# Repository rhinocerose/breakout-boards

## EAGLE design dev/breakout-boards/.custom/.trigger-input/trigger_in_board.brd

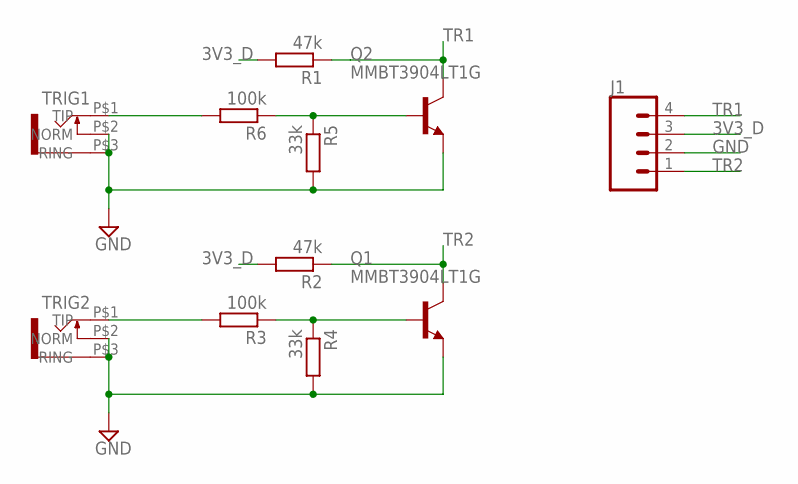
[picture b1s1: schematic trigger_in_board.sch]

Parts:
J1: CONN_04LOCK; 1X04_LOCK
Q1, Q2: MMBT3904LT1G; TRANSISTOR_SOT23-BEC
R1, R2: 47k; R0603
R3, R6: 100k; R0603
R4, R5: 33k; R0603
TRIG1, TRIG2: JACK_KOBICONN_PJM301DM_V2; KOBICONN_PJM301DM_JACK

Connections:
3V3_D: J1.3, R1.2, R2.2
GND: J1.2, Q1.E, Q2.E, R4.2, R5.2, TRIG1.P$2 (NORM), TRIG1.P$3 (RING), TRIG2.P$2 (NORM), TRIG2.P$3 (RING)
unnamed: R6.2, TRIG1.P$1 (TIP)
unnamed: Q2.B, R5.1, R6.1
unnamed: R3.2, TRIG2.P$1 (TIP)
unnamed: Q1.B, R3.1, R4.1
TR1: J1.4, Q2.C, R1.1
TR2: J1.1, Q1.C, R2.1

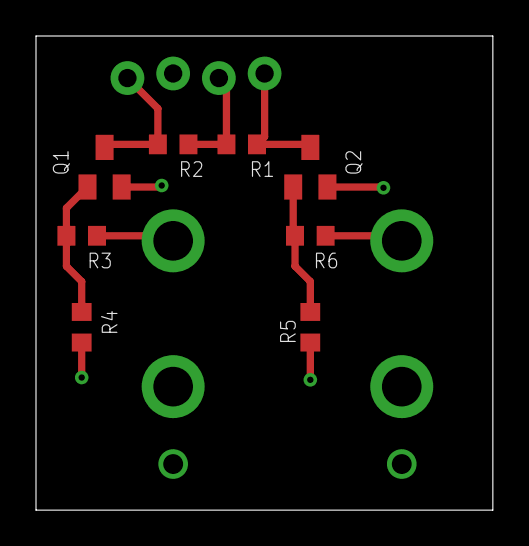
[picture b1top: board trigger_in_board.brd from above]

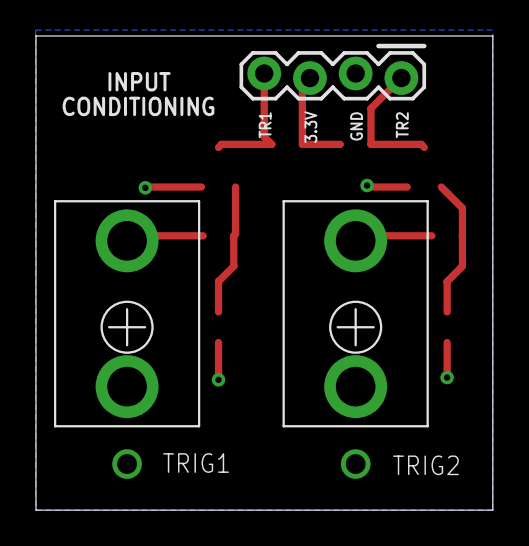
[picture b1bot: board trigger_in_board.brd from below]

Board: 2 copper layers, 25.4 x 26.3 mm, 11 parts (3 on the bottom side), 8 nets.

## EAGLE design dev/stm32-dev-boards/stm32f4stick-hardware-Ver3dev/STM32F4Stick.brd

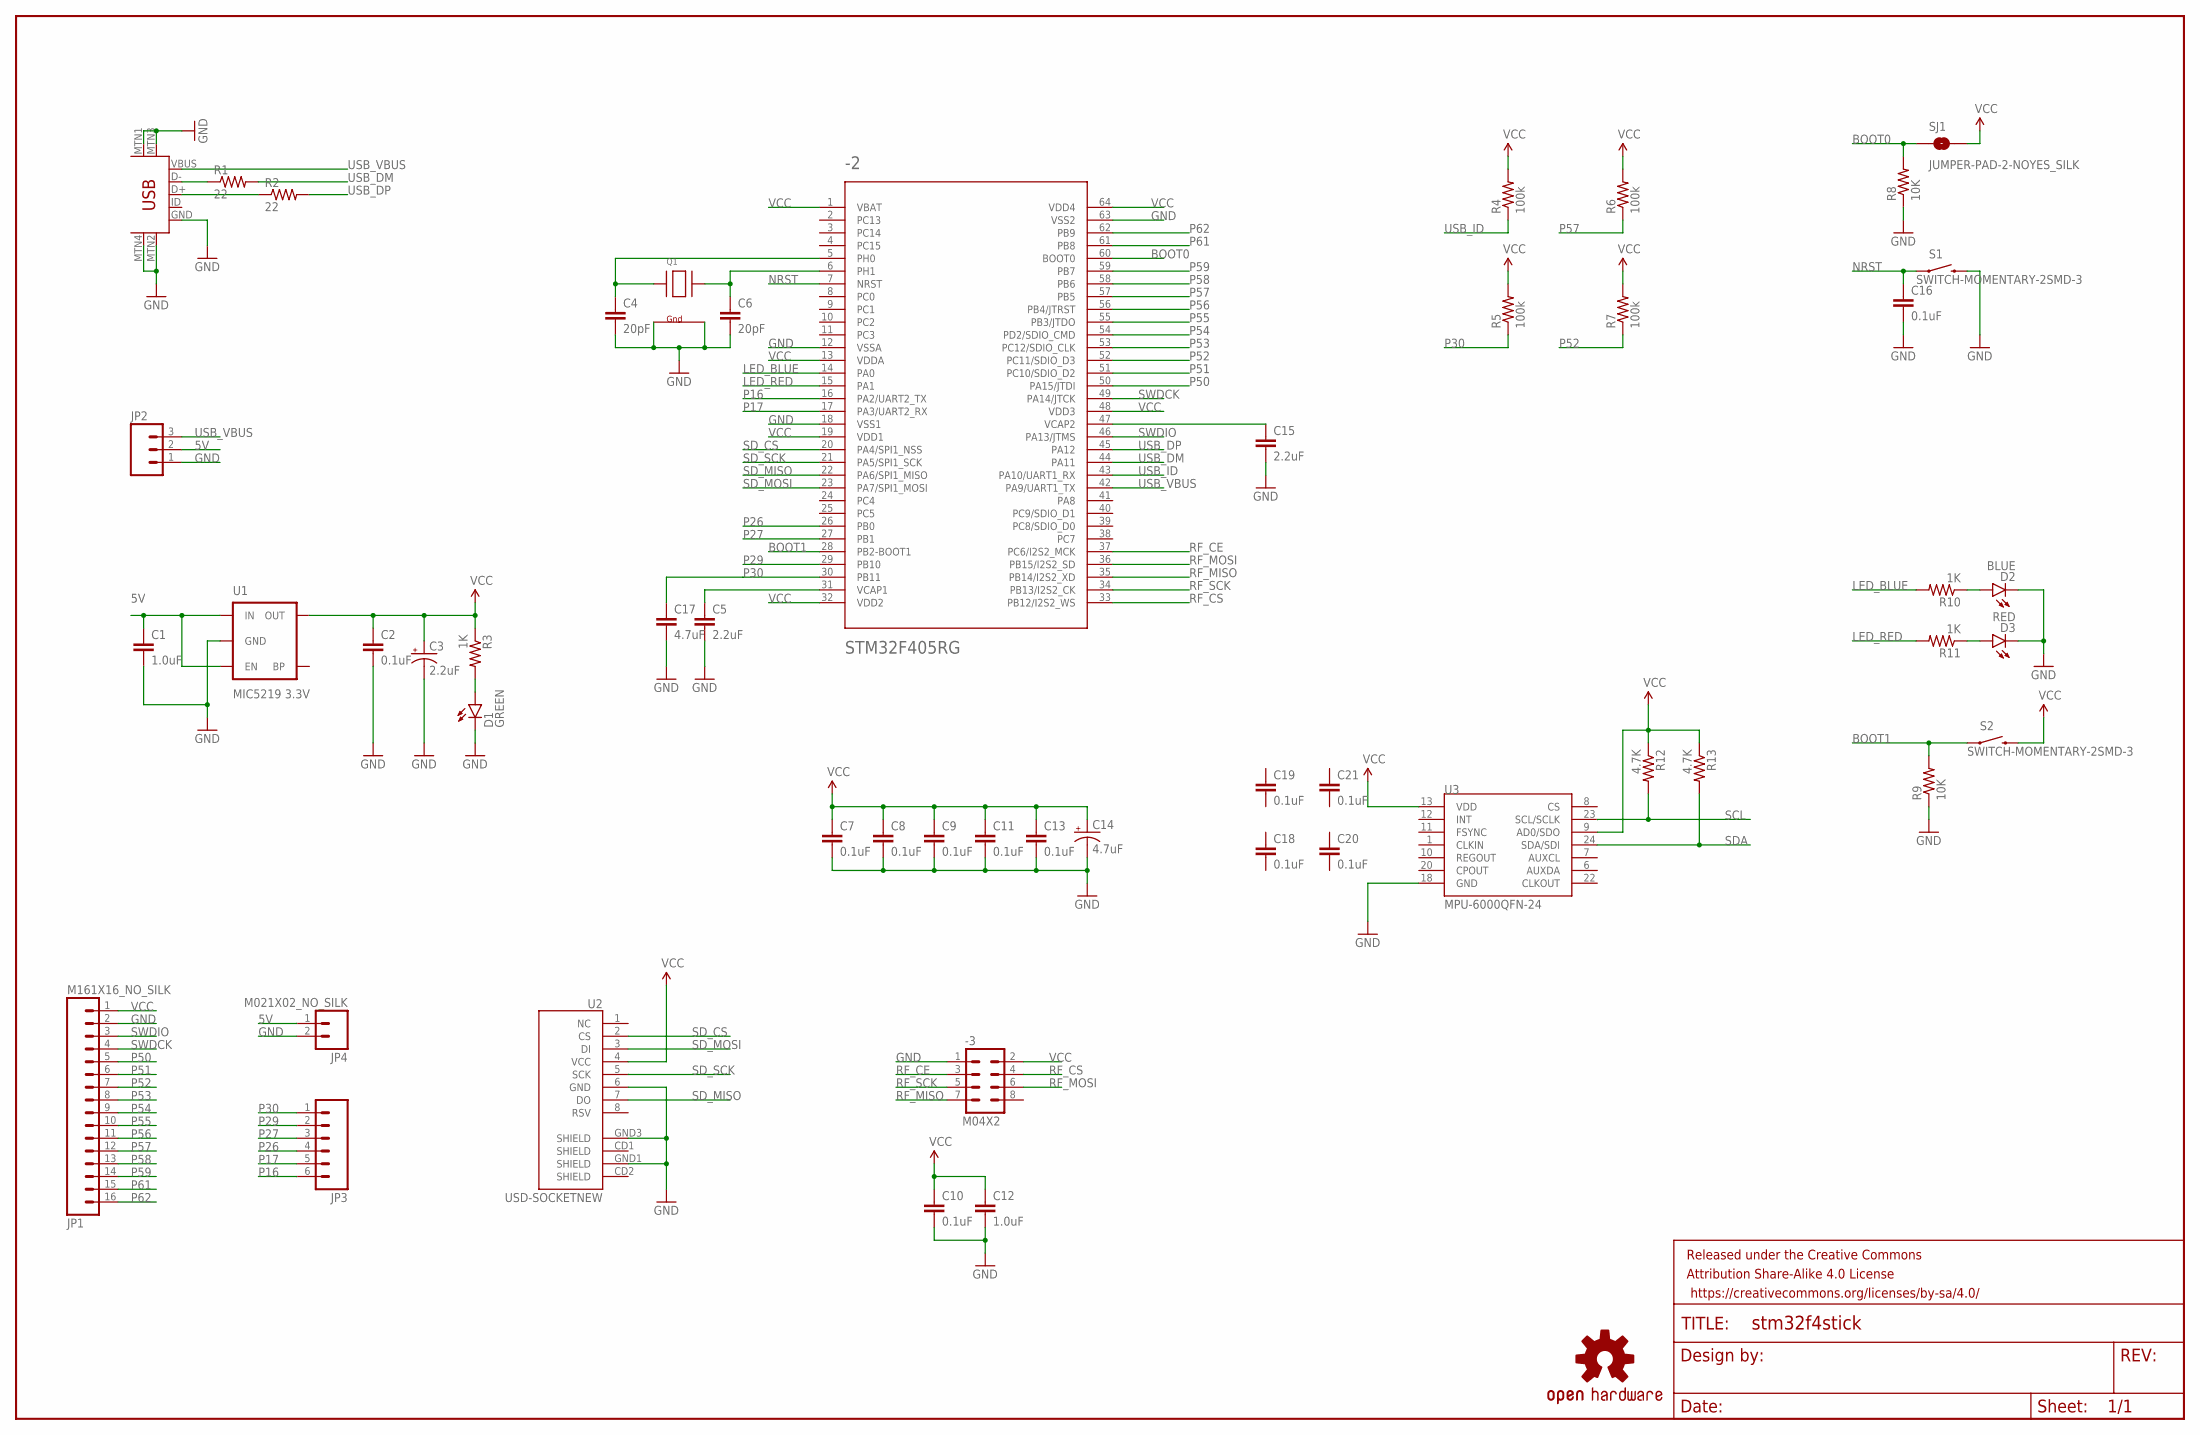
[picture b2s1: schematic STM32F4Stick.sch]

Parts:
-1: USB-MINIB-5PIN; USB-MINIB
-2: STM32F405RG; TQFP64
-3: M04X2; 2X4
C1, C12: 1.0uF; 0603-CAP
C2, C7, C8, C9, C10, C11, C13, C16, C18, C19, C20, C21: 0.1uF; 0603-CAP
C3: 2.2uF; EIA3216
C4, C6: 20pF; 0603-CAP
C5, C15: 2.2uF; 0603-CAP
C14: 4.7uF; EIA3216
C17: 4.7uF; 0603-CAP
D1: GREEN; LED-0603
D2: BLUE; LED-0603
D3: RED; LED-0603
FRAME1: FRAME-LEDGER; CREATIVE_COMMONS
JP1: M161X16_NO_SILK; 1X16_NO_SILK
JP2: M031X03_NO_SILK; 1X03_NO_SILK
JP3: M06NO_SILK; 1X06_NO_SILK
JP4: M021X02_NO_SILK; 1X02_NO_SILK
LOGO1: OSHW-LOGOM; OSHW-LOGO-M
Q1: XTAL-4-3225; NX3225
R1, R2: 22; 0603-RES
R3, R10, R11: 1K; 0603-RES
R4, R5, R6, R7: 100k; 0603-RES
R8, R9: 10K; 0603-RES
R12, R13: 4.7K; 0603-RES
S1, S2: SWITCH-MOMENTARY-2SMD-3; TACTILE_SWITCH_SMD-3
SJ1: JUMPER-PAD-2-NOYES_SILK; PAD-JUMPER-2-NO_YES_SILK
U1: MIC5219 3.3V; SOT23-5
U2: USD-SOCKETNEW; MICRO-SD-SOCKET-PP
U3: MPU-6000QFN-24; QFN-24-TESTING

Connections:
5V: C1.1, JP2.2, JP4.1, U1.1 (IN), U1.3 (EN)
BOOT0: -2.60 (BOOT0), R8.2, SJ1.1
BOOT1: -2.28 (PB2-BOOT1), R9.2, S2.1, S2.3 (1)
GND: -1.GND, -1.MTN1 (MTN2), -1.MTN2 (MTN3), -1.MTN3 (MTN1), -1.MTN4, -2.12 (VSSA), -2.18 (VSS1), -2.63 (VSS2), -3.1, C1.2, C2.2, C3.C (-), C4.2, C5.2, C6.2, C7.2, C8.2, C9.2, C10.2, C11.2, C12.2, C13.2, C14.C (-), C15.2, C16.2, C17.2, D1.C, D2.C, D3.C, JP1.2, JP2.1, JP4.2, Q1.2 (G2), Q1.4 (G1), R8.1, R9.1, S1.2, S1.4 (2), U1.2 (GND), U2.6 (GND), U2.GND1 (SHIELD), U2.GND3 (SHIELD), U3.18 (GND)
LED_BLUE: -2.14 (PA0), R10.2
LED_RED: -2.15 (PA1), R11.2
unnamed: -2.31 (VCAP1), C5.1
unnamed: -2.5 (PH0), C4.1, Q1.1 (X1)
unnamed: -2.6 (PH1), C6.1, Q1.3 (X2)
unnamed: -2.47 (VCAP2), C15.1
unnamed: D2.A, R10.1
unnamed: D3.A, R11.1
unnamed: D1.A, R3.2
unnamed: -1.D-, R1.1
unnamed: -1.D+, R2.1
NRST: -2.7 (NRST), C16.1, S1.1, S1.3 (1)
P16: -2.16 (PA2/UART2_TX), JP3.6
P17: -2.17 (PA3/UART2_RX), JP3.5
P26: -2.26 (PB0), JP3.4
P27: -2.27 (PB1), JP3.3
P29: -2.29 (PB10), JP3.2
P30: -2.30 (PB11), C17.1, JP3.1, R5.1
P50: -2.50 (PA15/JTDI), JP1.5
P51: -2.51 (PC10/SDIO_D2), JP1.6
P52: -2.52 (PC11/SDIO_D3), JP1.7, R7.1
P53: -2.53 (PC12/SDIO_CLK), JP1.8
P54: -2.54 (PD2/SDIO_CMD), JP1.9
P55: -2.55 (PB3/JTDO), JP1.10
P56: -2.56 (PB4/JTRST), JP1.11
P57: -2.57 (PB5), JP1.12, R6.1
P58: -2.58 (PB6), JP1.13
P59: -2.59 (PB7), JP1.14
P61: -2.61 (PB8), JP1.15
P62: -2.62 (PB9), JP1.16
RF_CE: -2.37 (PC6/I2S2_MCK), -3.3
RF_CS: -2.33 (PB12/I2S2_WS), -3.4
RF_MISO: -2.35 (PB14/I2S2_XD), -3.7
RF_MOSI: -2.36 (PB15/I2S2_SD), -3.6
RF_SCK: -2.34 (PB13/I2S2_CK), -3.5
SCL: R12.2, U3.23 (SCL/SCLK)
SDA: R13.2, U3.24 (SDA/SDI)
SD_CS: -2.20 (PA4/SPI1_NSS), U2.2 (CS)
SD_MISO: -2.22 (PA6/SPI1_MISO), U2.7 (DO)
SD_MOSI: -2.23 (PA7/SPI1_MOSI), U2.3 (DI)
SD_SCK: -2.21 (PA5/SPI1_SCK), U2.5 (SCK)
SWDCK: -2.49 (PA14/JTCK), JP1.4
SWDIO: -2.46 (PA13/JTMS), JP1.3
USB_DM: -2.44 (PA11), R1.2
USB_DP: -2.45 (PA12), R2.2
USB_ID: -2.43 (PA10/UART1_RX), R4.1
USB_VBUS: -1.VBUS, -2.42 (PA9/UART1_TX), JP2.3
VCC: -2.1 (VBAT), -2.13 (VDDA), -2.19 (VDD1), -2.32 (VDD2), -2.48 (VDD3), -2.64 (VDD4), -3.2, C2.1, C3.A (+), C7.1, C8.1, C9.1, C10.1, C11.1, C12.1, C13.1, C14.A (+), JP1.1, R3.1, R4.2, R5.2, R6.2, R7.2, R12.1, R13.1, S2.2, S2.4 (2), SJ1.2, U1.5 (OUT), U2.4 (VCC), U3.9 (AD0/SDO), U3.13 (VDD)

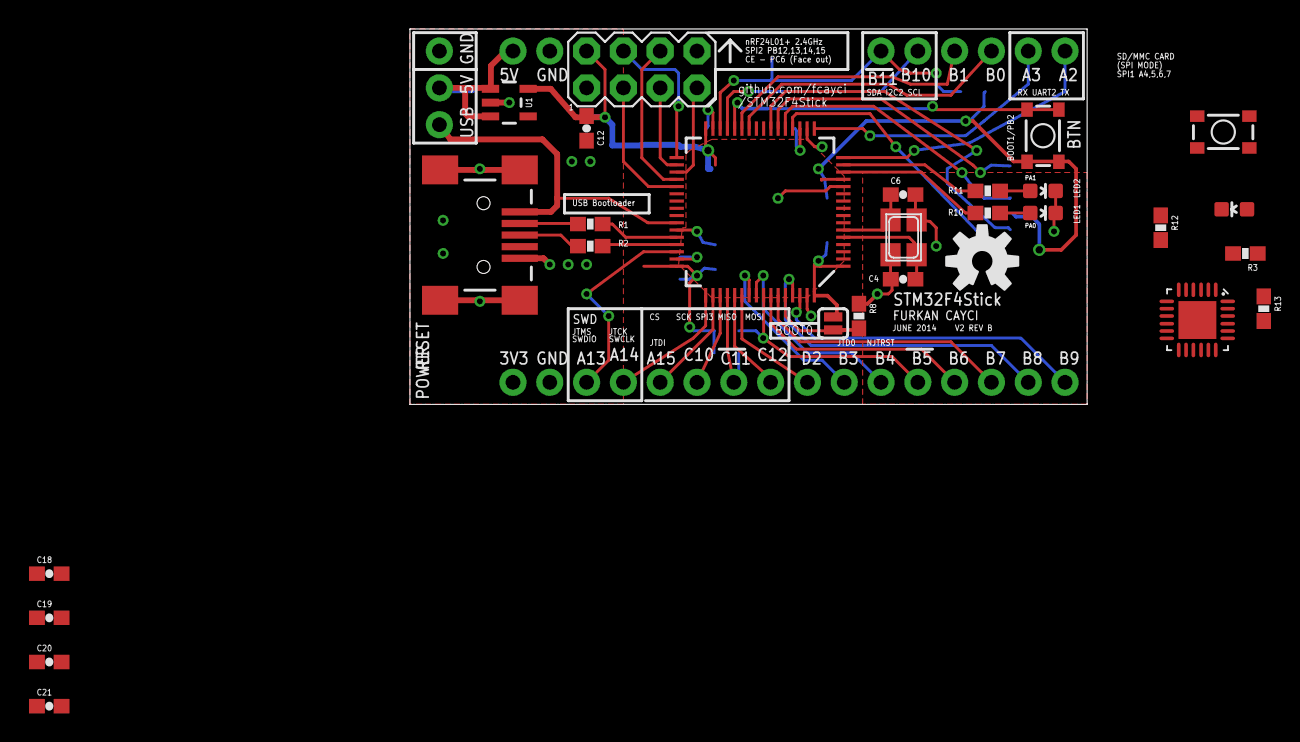
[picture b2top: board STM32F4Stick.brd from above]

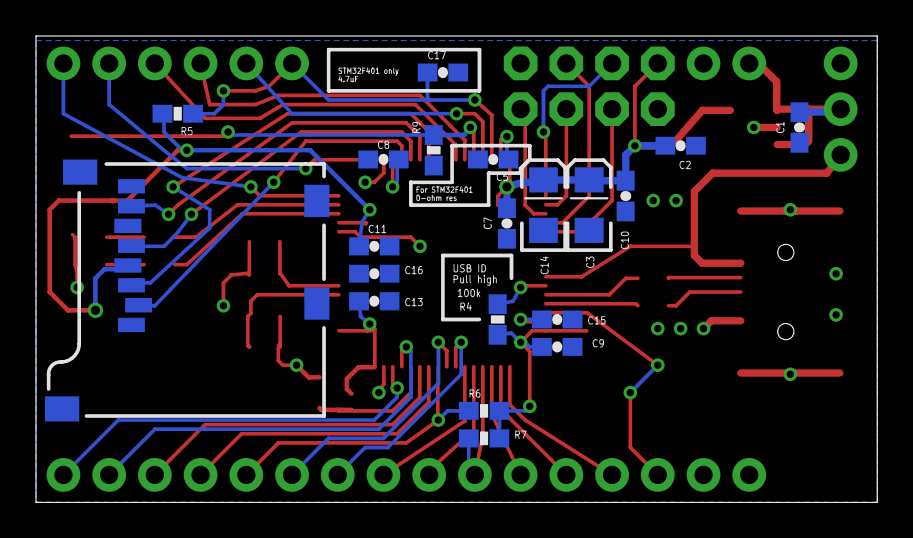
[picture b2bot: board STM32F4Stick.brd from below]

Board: 2 copper layers, 46.7 x 25.9 mm, 53 parts (20 on the bottom side), 52 nets.

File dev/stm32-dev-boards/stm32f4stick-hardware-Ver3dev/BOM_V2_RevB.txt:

Partlist exported from /Users/furkan/workcenter/eagle/projects/STM32F4Stick/STM32F4Stick.sch at 7/10/14 2:12 AM

Part   Value                   Device                   Package                  Description          
-1     USB-MINIB-5PIN          USB-MINIB-5PIN           USB-MINIB                Mini-USB "B" connect 
-2     STM32F405RG             STM32F405RG              TQFP64                   ARM DSP Chip used on 
-3     M04X2                   M04X2                    2X4                      .1" header, two rows 
C1     1.0uF                   1.0UF-16V-10%(0603)      0603-CAP                 CAP-00868            
C2     0.1uF                   0.1UF-25V-5%(0603)       0603-CAP                 CAP-08604            
C3     2.2uF                   CAP_POL1206              EIA3216                  Capacitor Polarized  
C4     20pF                    12PF-50V-5%(0603)        0603-CAP                 CAP-09137            
C5     2.2uF                   2.2UF-10V-20%(0603)      0603-CAP                 CAP-07888            
C6     20pF                    12PF-50V-5%(0603)        0603-CAP                 CAP-09137            
C7     0.1uF                   0.1UF-25V-5%(0603)       0603-CAP                 CAP-08604            
C8     0.1uF                   0.1UF-25V-5%(0603)       0603-CAP                 CAP-08604            
C9     0.1uF                   0.1UF-25V-5%(0603)       0603-CAP                 CAP-08604            
C10    0.1uF                   0.1UF-25V-5%(0603)       0603-CAP                 CAP-08604            
C11    0.1uF                   0.1UF-25V-5%(0603)       0603-CAP                 CAP-08604            
C12    1.0uF                   1.0UF-16V-10%(0603)      0603-CAP                 CAP-00868            
C13    0.1uF                   0.1UF-25V-5%(0603)       0603-CAP                 CAP-08604            
C14    4.7uF                   CAP_POL1206              EIA3216                  Capacitor Polarized  
C15    2.2uF                   2.2UF-10V-20%(0603)      0603-CAP                 CAP-07888            
C16    0.1uF                   0.1UF-25V-5%(0603)       0603-CAP                 CAP-08604            
C17    4.7uF                   4.7UF-6.3V-10%(0603)0603 0603-CAP                 CAP-08280            
D1     GREEN                   LED-GREEN0603            LED-0603                 Various green LEDs   
D2     BLUE                    LED-BLUE0603             LED-0603                 Blue LEDs for produc 
D3     RED                     LED-RED0603              LED-0603                 Assorted Red LEDs    
FRAME1 FRAME-LEDGER            FRAME-LEDGER             CREATIVE_COMMONS         Schematic Frame      
JP1    M161X16_NO_SILK         M161X16_NO_SILK          1X16_NO_SILK             1x16 .1" header      
JP2                            M031X03_NO_SILK          1X03_NO_SILK             Header 3             
JP3                            M06NO_SILK               1X06_NO_SILK             Header 6             
JP4    M021X02_NO_SILK         M021X02_NO_SILK          1X02_NO_SILK             Standard 2-pin 0.1"  
LOGO1  OSHW-LOGOM              OSHW-LOGOM               OSHW-LOGO-M              Open Source Hardware 
Q1                             XTAL-4-3225              NX3225                   Classic 4-pin 3.2 x  
R1     22                      22OHM1/10W1%(0603)       0603-RES                 RES-08698            
R2     22                      22OHM1/10W1%(0603)       0603-RES                 RES-08698            
R3     1K                      1KOHM1/10W1%(0603)       0603-RES                 RES-07856            
R4     100k                    100KOHM1/10W1%(0603)     0603-RES                 RES-07828            
R5     100k                    100KOHM1/10W1%(0603)     0603-RES                 RES-07828            
R6     100k                    100KOHM1/10W1%(0603)     0603-RES                 RES-07828            
R7     100k                    100KOHM1/10W1%(0603)     0603-RES                 RES-07828            
R8     10K                     10KOHM1/10W1%(0603)0603  0603-RES                 RES-00824            
R9     10K                     10KOHM1/10W1%(0603)0603  0603-RES                 RES-00824            
R10    1K                      1KOHM1/10W1%(0603)       0603-RES                 RES-07856            
R11    1K                      1KOHM1/10W1%(0603)       0603-RES                 RES-07856            
S1     SWITCH-MOMENTARY-2SMD-3 SWITCH-MOMENTARY-2SMD-3  TACTILE_SWITCH_SMD-3     Various NO switches- 
S2     SWITCH-MOMENTARY-2SMD-3 SWITCH-MOMENTARY-2SMD-3  TACTILE_SWITCH_SMD-3     Various NO switches- 
SJ1    JUMPER-PAD-2-NOYES_SILK JUMPER-PAD-2-NOYES_SILK  PAD-JUMPER-2-NO_YES_SILK                      
U1     MIC5219 3.3V            V_REG_MIC52193.3V        SOT23-5                  V_REG MIC5219        
U2     USD-SOCKETNEW           USD-SOCKETNEW            MICRO-SD-SOCKET-PP       microSD Socket

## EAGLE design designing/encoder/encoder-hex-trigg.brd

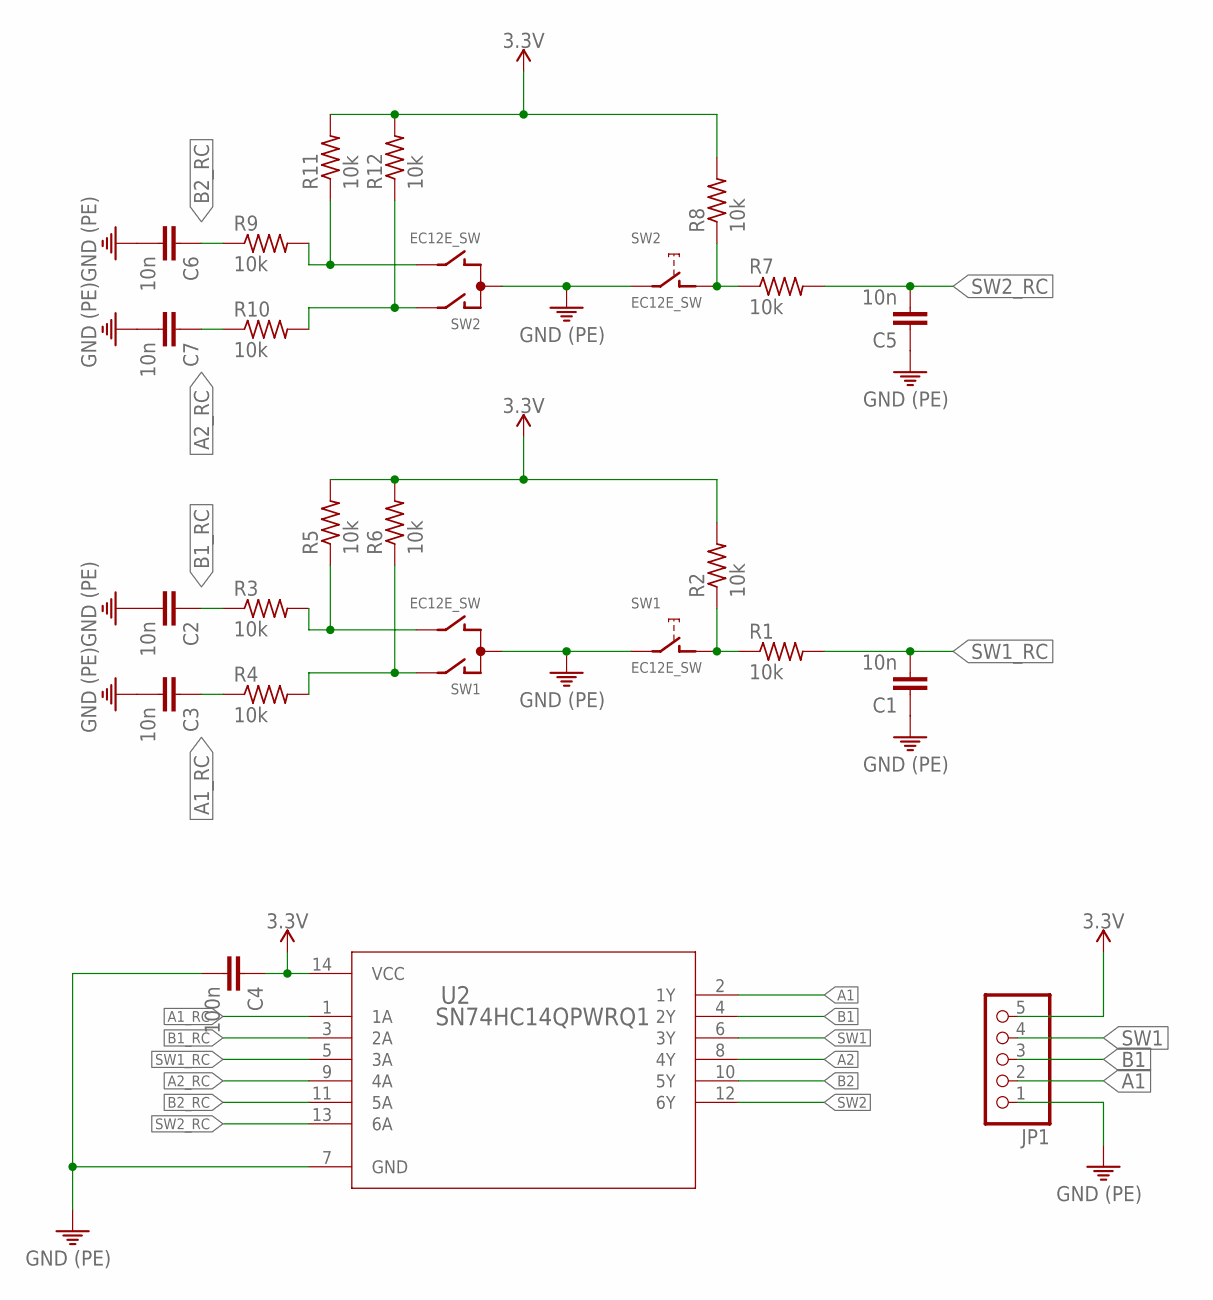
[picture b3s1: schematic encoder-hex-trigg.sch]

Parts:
C1, C2, C3, C5, C6, C7: 10n; C0603
C4: 100n; C0603
JP1: PINHD-1X5; 1X05
R1, R2, R3, R4, R5, R6, R7, R8, R9, R10, R11, R12: 10k; R0603
SW1, SW2: EC12E_SW; ALPS_EC12E_SW
U2: SN74HC14QPWRQ1; PW14

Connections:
3.3V: C4.1, JP1.5, R2.2, R5.2, R6.2, R8.2, R11.2, R12.2, U2.14 (VCC)
A1: JP1.2, U2.2 (1Y)
A1_RC: C3.1, R4.1, U2.1 (1A)
A2: U2.8 (4Y)
A2_RC: C7.1, R10.1, U2.9 (4A)
B1: JP1.3, U2.4 (2Y)
B1_RC: C2.1, R3.1, U2.3 (2A)
B2: U2.10 (5Y)
B2_RC: C6.1, R9.1, U2.11 (5A)
unnamed: R1.1, R2.1, SW1.D (1)
unnamed: R7.1, R8.1, SW2.D (1)
unnamed: R3.2, R5.1, SW1.B
unnamed: R4.2, R6.1, SW1.A
unnamed: R9.2, R11.1, SW2.B
unnamed: R10.2, R12.1, SW2.A
PE: C1.1, C2.2, C3.2, C4.2, C5.1, C6.2, C7.2, JP1.1, SW1.C, SW1.E (2), SW2.C, SW2.E (2), U2.7 (GND)
SW1: JP1.4, U2.6 (3Y)
SW1_RC: C1.2, R1.2, U2.5 (3A)
SW2: U2.12 (6Y)
SW2_RC: C5.2, R7.2, U2.13 (6A)

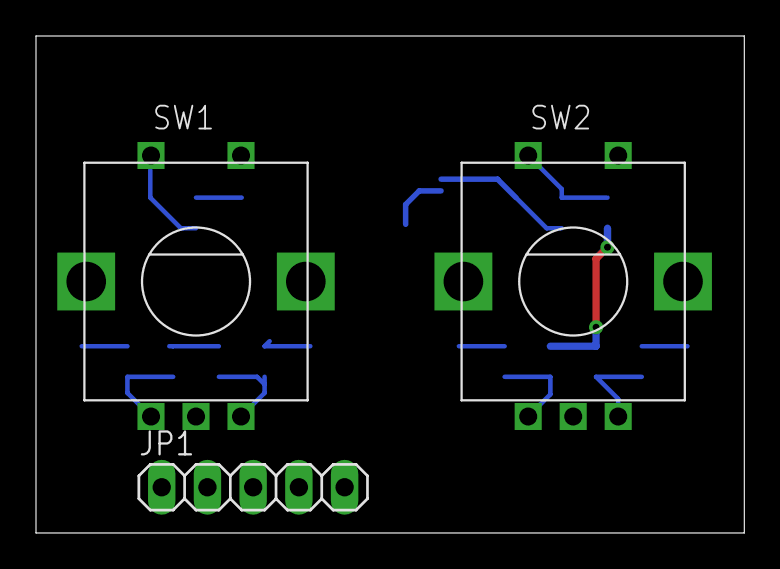
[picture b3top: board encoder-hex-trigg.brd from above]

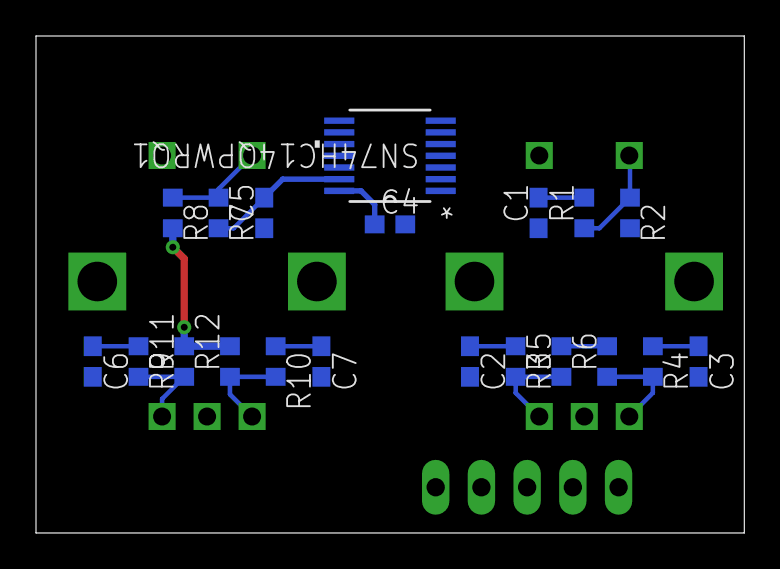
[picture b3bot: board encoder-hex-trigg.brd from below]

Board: 2 copper layers, 39.4 x 27.6 mm, 23 parts (20 on the bottom side), 17 nets.

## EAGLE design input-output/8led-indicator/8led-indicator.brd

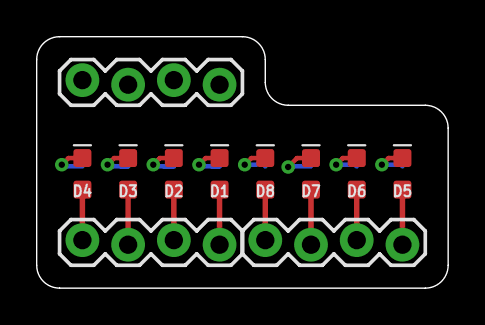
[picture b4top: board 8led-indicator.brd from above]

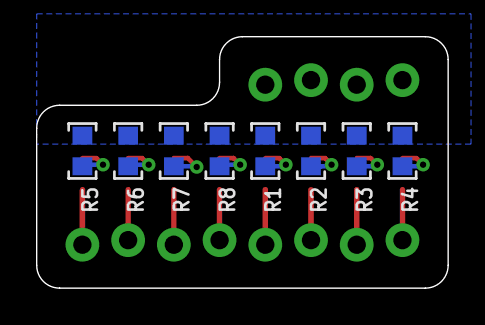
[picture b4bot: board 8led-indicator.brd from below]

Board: 2 copper layers, 22.9 x 14.0 mm, 19 parts (8 on the bottom side), 17 nets.

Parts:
D1, D2, D3, D4, D5, D6, D7, D8: LED-0603
J1, J2, J3: 1X04_LOCK
R1, R2, R3, R4, R5, R6, R7, R8: R0603

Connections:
GND: J3.1, J3.2, J3.3, J3.4, R1.1, R2.1, R3.1, R4.1, R5.1, R6.1, R7.1, R8.1
unnamed: D1.A, J1.4
unnamed: D2.A, J1.3
unnamed: D3.A, J1.2
unnamed: D4.A, J1.1
unnamed: D1.C, R1.2
unnamed: D2.C, R2.2
unnamed: D3.C, R3.2
unnamed: D4.C, R4.2
unnamed: D5.A, J2.4
unnamed: D6.A, J2.3
unnamed: D7.A, J2.2
unnamed: D8.A, J2.1
unnamed: D5.C, R5.2
unnamed: D6.C, R6.2
unnamed: D7.C, R7.2
unnamed: D8.C, R8.2

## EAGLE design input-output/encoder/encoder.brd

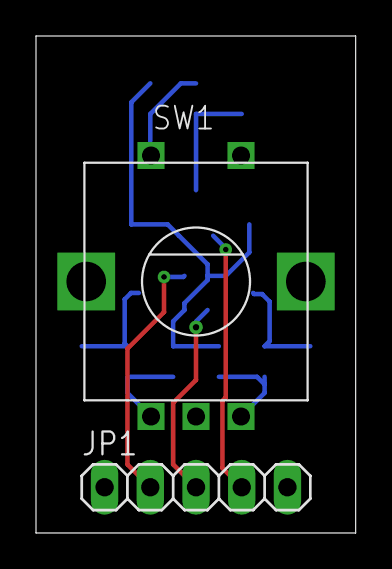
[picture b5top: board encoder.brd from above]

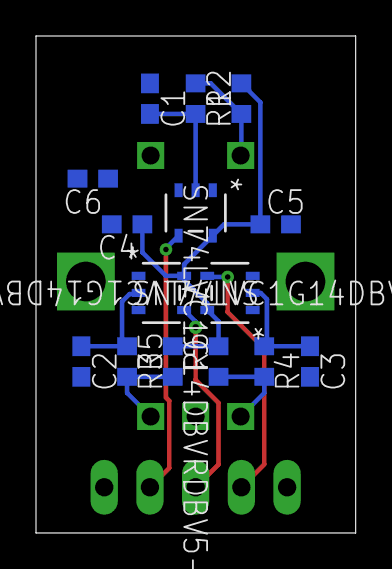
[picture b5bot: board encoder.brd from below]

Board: 2 copper layers, 17.8 x 27.6 mm, 17 parts (15 on the bottom side), 11 nets.

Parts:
C1, C2, C3: 10n; C0603
C4, C5, C6: 100n; C0603
JP1: 1X05
R1, R2, R3, R4, R5, R6: 10k; R0603
SW1: EC12E_SW; ALPS_EC12E_SW
U1, U2, U3: SN74LVC1G14DBVRDBV5-L; DBV5-L

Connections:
3.3V: C4.1, C5.1, C6.1, JP1.5, R2.2, R5.2, R6.2, U1.5, U2.5, U3.5
A: JP1.2, U2.4
A_RC: C3.1, R4.1, U2.2
B: JP1.3, U3.4
B_RC: C2.1, R3.1, U3.2
unnamed: R1.1, R2.1, SW1.D
unnamed: R3.2, R5.1, SW1.B
unnamed: R4.2, R6.1, SW1.A
PE: C1.1, C2.2, C3.2, C4.2, C5.2, C6.2, JP1.1, SW1.C, SW1.E, U1.1, U1.3, U2.1, U2.3, U3.1, U3.3
SW: JP1.4, U1.4
SW_RC: C1.2, R1.2, U1.2

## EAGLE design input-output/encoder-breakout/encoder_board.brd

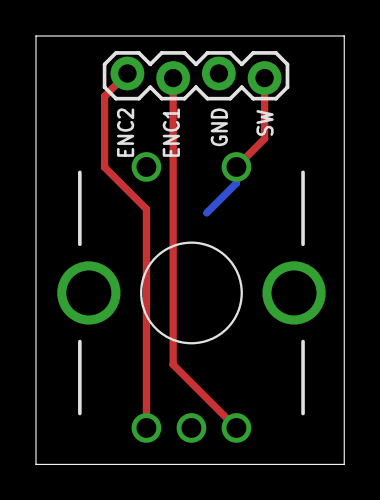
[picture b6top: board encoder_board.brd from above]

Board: 2 copper layers, 17.1 x 23.8 mm, 3 parts (1 on the bottom side), 4 nets.

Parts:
C15: 470n; C0603
ENC-R: PEC11R; PEC11R-4XXXK-SXXXX
J1: 1X04_LOCK

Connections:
ENC_R1: ENC-R.B, J1.2
ENC_R2: ENC-R.A, J1.1
GND: C15.1, ENC-R.C, ENC-R.SH1, ENC-R.SH2, ENC-R.SW1, J1.3
SW_R: C15.2, ENC-R.SW2, J1.4

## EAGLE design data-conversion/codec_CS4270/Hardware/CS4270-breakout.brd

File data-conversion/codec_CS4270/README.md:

# CS 4270 105 dB Stereo Codec

​          

###                    [CS4270 Product Data Sheet](https://statics.cirrus.com/pubs/proDatasheet/CS4270_DS686F2.pdf)

The CS4270 is a stereo audio codec  with single-ended inputs and outputs, and a dynamic range of 105 dB and  THD+N of -95 dB. Requiring a minimal set of passive external components, the CS4270 provides designers with a simple solution that reduces the  bill-of-materials cost and the required space on their printed circuit  board. Configuring the IC through an industry standard control port  provides access to additional features such as logarithmic digital  volume control. The CS4270 utilizes Popguard® technology for controlling clicks and pops associated with power cycling, which eliminates external mute control circuitry.

### Technology

[Mono/Stereo Codecs](https://www.cirrus.com/products/cs4270/#loadTechnology;)

### Features

- Complete stereo codec
- 24-bit conversion
- System sampling rates up to 216 kHz
- Multibit Delta Sigma modulator architecture
- 105 dB dynamic range (A-weighted)
- -95 dB THD+N
- Single-ended input/output architecture
- Output digital volume control, 0.5 dB steps
- Integrated level shifters for direct interface to logic levels from 1.8V to 5.0V
- 3.3 or 5 V core power supply (VD)
- Cirrus Logic Popguard technology
- Available in 24-pin TSSOP package
- Stand alone or control part functionality
- Consumer and automotive D-grade availability

## Parametric Specifications

| **Channels In**                        | 2        |
| -------------------------------------- | -------- |
| **Channels Out**                       | 2        |
| **DAC THD+N (dB)**                     | -87      |
| **ADC THD+N (dB)**                     | -95      |
| **Analog Power Supply (V)**            | 5        |
| **Digital Power Supply (V)**           | 3.3-5    |
| **Logic Power Supply (V)**             | 1.8-5    |
| **Operational Power Consumption (mW)** | 224-345  |
| **Package**                            | 24 TSSOP |

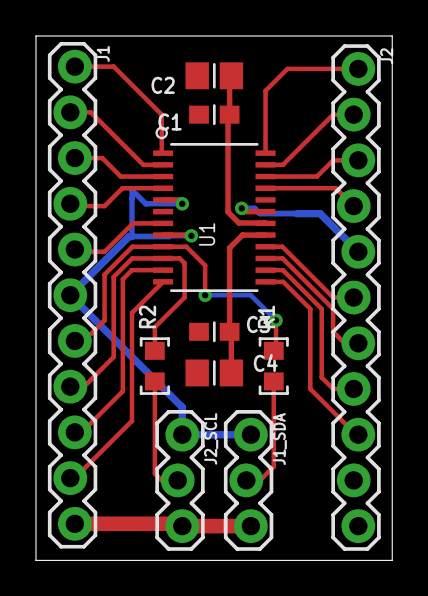
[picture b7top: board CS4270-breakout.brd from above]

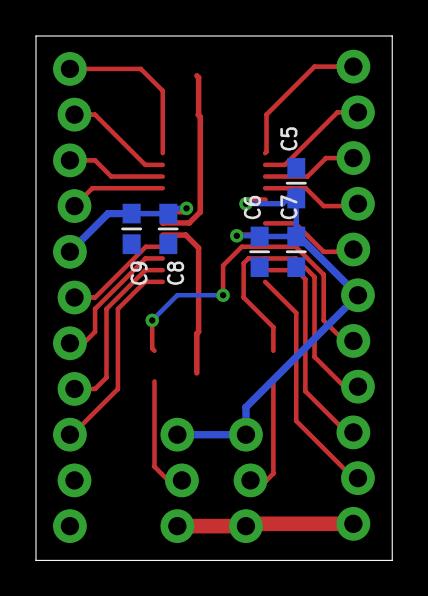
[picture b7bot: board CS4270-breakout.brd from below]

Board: 2 copper layers, 19.8 x 29.1 mm, 16 parts (5 on the bottom side), 25 nets.

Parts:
C1, C3, C5, C6, C7, C8, C9: C0603
C2, C4: C0805
J1, J2: 1X11_LOCK
J1_SDA, J2_SCL: 1X03_LOCK
R1, R2: R0603
U1: CS4270-CZZCIR-TSSOP-24-L; CIR-TSSOP-24-L

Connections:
+3V3: C5.1, C6.2, C7.2, J1.6, J1_SDA.1, J2_SCL.1, U1.5, U1.8
+5V: C8.1, C9.1, J2.5, U1.19
AD0: J1.9, U1.11
AGND: C1.2, C2.2, C3.1, C4.1, C6.1, C7.1, C8.2, C9.2, J2.10, J2.11, U1.20
AINA: J2.7, U1.15
AINB: J2.6, U1.16
AOUTA: J2.3, U1.22
AOUTB: J2.2, U1.23
DGND: C5.2, J1.11, J1_SDA.3, J2_SCL.3, U1.6
LRCK: J1.2, U1.2
MCLK: J1.3, U1.3
MDIV1: J1.10, U1.12
MDIV2: J2.9, U1.13
MUTEA: J2.4, U1.21
MUTEB: J2.1, U1.24
unnamed: J1_SDA.2, R1.1
unnamed: C1.1, C2.1, U1.18
unnamed: C3.2, C4.2, U1.17
unnamed: J2_SCL.2, R2.1
RST: J2.8, U1.14
SCL: J1.8, R2.2, U1.10
SCLK: J1.4, U1.4
SDA: J1.7, R1.2, U1.9
SDIN: J1.1, U1.1
SDOUT: J1.5, U1.7

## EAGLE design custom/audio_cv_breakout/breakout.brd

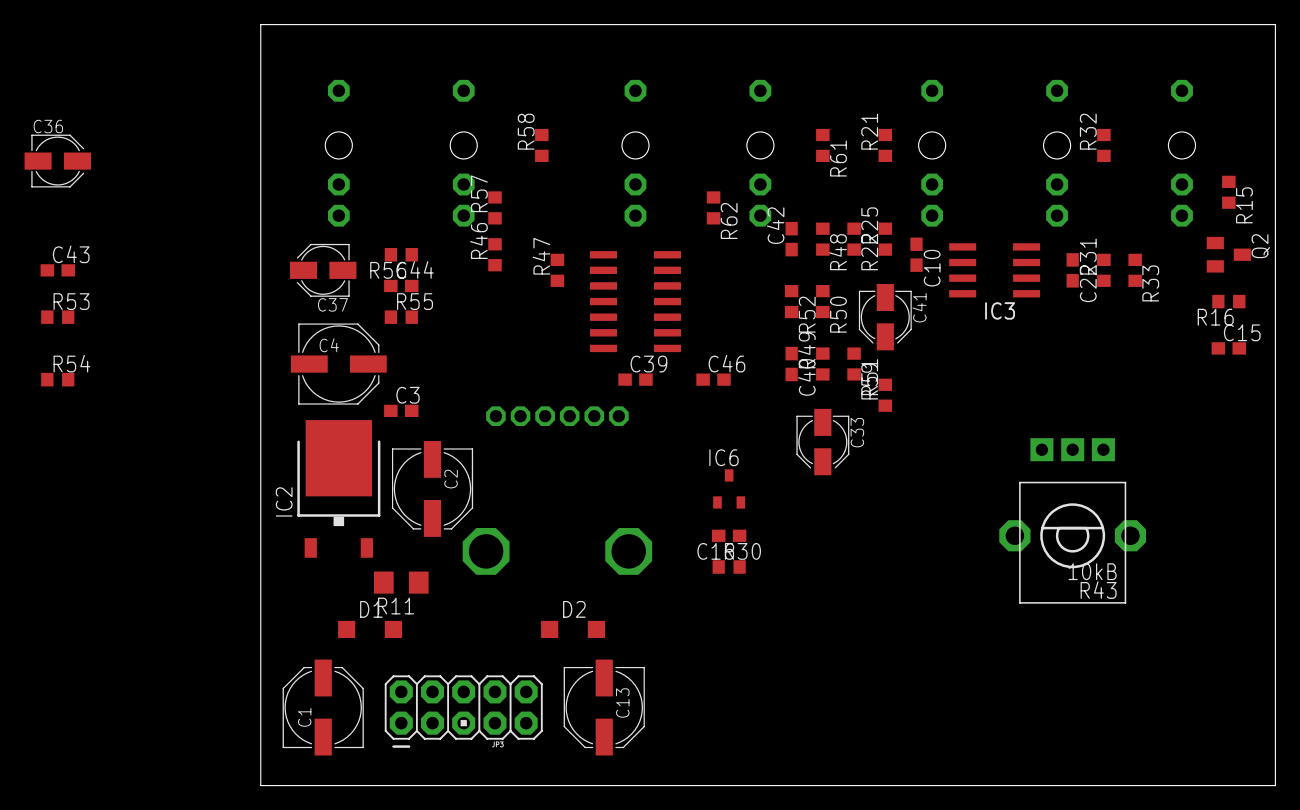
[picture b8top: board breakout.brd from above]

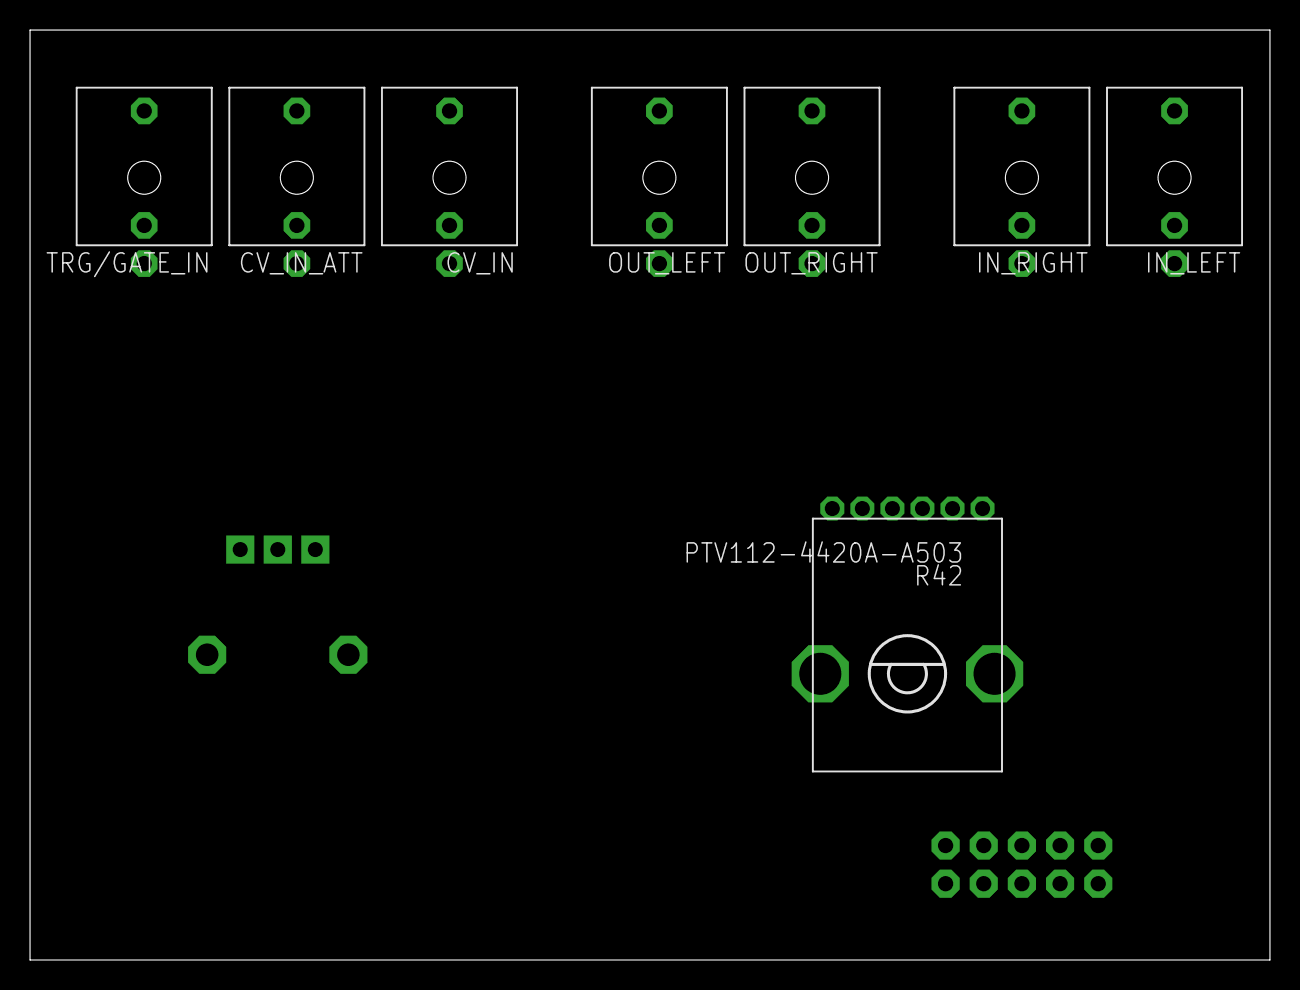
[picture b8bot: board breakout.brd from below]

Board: 2 copper layers, 82.5 x 61.9 mm, 62 parts (8 on the bottom side), 36 nets, no tracks yet.

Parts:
C1, C2, C4, C13: 47u; PANASONIC_D
C3, C15, C16, C39, C46: 100n; C0603
C10, C22: 1n; C0603
C33, C36, C37, C41: 10u; PANASONIC_B
C40, C42: 18p; C0603
C43, C44: 220p; C0603
CV_IN: PJ301_THONKICONN6; WQP_PJ_301M6
CV_IN_ATT: PJ301_THONKICONN6; WQP_PJ_301M6
D1, D2: 1N5819HW; SOD123
IC1: OPAMP-TL074D; SO14
IC2: LM1117-3.3; TO252
IC3: MCP6002; SO08
IC6: LM4040B10; DBZ_R-PDSO-G3
IN_LEFT: PJ301_THONKICONN6; WQP_PJ_301M6
IN_RIGHT: PJ301_THONKICONN6; WQP_PJ_301M6
JP3: M05X2PTH; AVR_ICSP
OUT_LEFT: PJ301_THONKICONN6; WQP_PJ_301M6
OUT_RIGHT: PJ301_THONKICONN6; WQP_PJ_301M6
Q2: MMBT3904; SOT23-BEC
R11: 4.7; R1206
R15, R21, R32: 100k; R0603
R16: 10k; R0603
R22, R33: 200k; R0603
R25: 33k; R0603
R30: 470; R0603
R31: 66.5k; R0603
R42: PTV112-4420A-A503; BOURNS_PTV112
R43: 10kB; ALPS_POT_VERTICAL_PS
R46, R47: 3.3k; R0603
R48, R49, R50, R59: 39k; R0603
R51, R52, R53, R54, R55, R56: 5.6k; R0603
R57, R58: 22k; R0603
R61, R62: 1.0k; R0603
TRG/GATE_IN: PJ301_THONKICONN6; WQP_PJ_301M6

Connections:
+3V3: C3.1, C4.+, C15.1, IC2.3, IC3.8, R16.2
AREF_-10: C16.1, IC6.2, R22.2, R30.2, R43.P$3
DENSITY_CV: C22.2, IC3.1, R31.1
GND: C1.-, C2.-, C3.2, C4.-, C13.+, C15.2, C16.2, C39.2, C43.2, C44.2, C46.1, CV_IN.P1, CV_IN_ATT.P1, IC1.3, IC1.5, IC1.10, IC1.12, IC2.1, IC3.3, IC3.4, IC3.5, IC6.1, IN_LEFT.P1, IN_RIGHT.P1, JP3.3, JP3.4, JP3.5, JP3.6, JP3.7, JP3.8, OUT_LEFT.P1, OUT_RIGHT.P1, Q2.E, R43.P$1, R50.1, R54.1, R56.1, R59.1, TRG/GATE_IN.P1, TRG/GATE_IN.P2
LOUT_JACK: OUT_LEFT.P3, R61.1
unnamed: CV_IN.P3, R21.2
unnamed: C10.1, IC3.6, R21.1, R22.1, R25.2
unnamed: CV_IN_ATT.P3, R32.2
unnamed: C37.-, C44.1, R55.1, R56.2
unnamed: IN_RIGHT.P3, R58.2
unnamed: IN_LEFT.P3, IN_RIGHT.P2, R57.2
unnamed: C36.-, C43.1, R53.1, R54.2
unnamed: C41.-, R50.2, R52.2
unnamed: C22.1, IC3.2, R31.2, R32.1, R33.1
unnamed: C42.1, IC1.13, R48.2, R52.1
unnamed: R33.2, R43.P$2
unnamed: C42.2, IC1.14, R48.1, R62.2
unnamed: C33.-, R51.2, R59.2
unnamed: C40.1, IC1.9, R49.2, R51.1
unnamed: C40.2, IC1.8, R49.1, R61.2
unnamed: R15.1, TRG/GATE_IN.P3
unnamed: Q2.B, R15.2
unnamed: IC1.7, R42.2P, R42.3P, R53.2
unnamed: IC1.1, R42.2, R42.3, R55.2
unnamed: R42.1P, R47.1
unnamed: R42.1, R46.1
unnamed: IC1.6, R47.2, R58.1
unnamed: C2.+, IC2.2, R11.2
unnamed: D1.A, JP3.1, JP3.2
unnamed: IC1.2, R46.2, R57.1
unnamed: D2.C, JP3.9, JP3.10
PLAY: Q2.C, R16.1
ROUT_JACK: OUT_RIGHT.P3, R62.1
SIZE_CV: C10.2, IC3.7, R25.1
VCC: C1.+, C39.1, D1.C, IC1.4, R11.1
VEE: C13.-, C46.2, D2.A, IC1.11, R30.1

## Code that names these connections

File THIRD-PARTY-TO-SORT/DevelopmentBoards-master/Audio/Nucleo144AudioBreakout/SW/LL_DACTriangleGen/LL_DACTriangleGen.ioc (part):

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Mcu.Name=STM32F767ZITx
Mcu.Package=LQFP144
Mcu.UserName=STM32F767ZITx
PA0/WKUP.Signal=ADCx_IN0
PA1.Signal=ADCx_IN1
PA4.Signal=COMP_DAC1_group
PA5.Signal=COMP_DAC2_group
RCC.HSE_VALUE=25000000
RCC.SYSCLKFreq_VALUE=216000000
RCC.SYSCLKSource=RCC_SYSCLKSOURCE_PLLCLK
board=custom

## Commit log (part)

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2022-04-17 Only reset left to sort out
2022-04-17 Encoders added
2022-04-17 Added SD breakout
2022-04-17 Added pdf and images
2022-04-17 Added images
2022-04-18 Added accelerometer
2022-04-18 Added codecs
2022-04-19 Added dual encoder module
2022-04-19 Added datasheets and firmware
2022-04-19 Added DAC buffers to AD1938
2022-11-23 Dev folder added
2022-12-05 Renamed folders to not be hidden
2023-01-02 Added encoder
2023-01-02 Added I2C encoder
2023-02-06 Rearranged
2024-02-08 Added Nucleo base board
2024-11-15 Added Arduino Nano breakout
2025-08-12 Update submodules to track main branch
2025-08-12 Update submodules: set branch=main and fix URLs
2025-08-12 Update submodules: add branch=main and fix URLs
2025-08-13 Remove .gitmodules (no submodules exist)

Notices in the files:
parts and their libraries:
SparkFun-Connectors: Licensing: Creative Commons ShareAlike 4.0 International - https://creativecommons.org/licenses/by-sa/4.0
COPYRIGHT: Copyright (C) 2022 Ultra Librarian. All rights reserved.
SparkFun-Aesthetics: Released under the Creative Commons Attribution Share-Alike 4.0 License
